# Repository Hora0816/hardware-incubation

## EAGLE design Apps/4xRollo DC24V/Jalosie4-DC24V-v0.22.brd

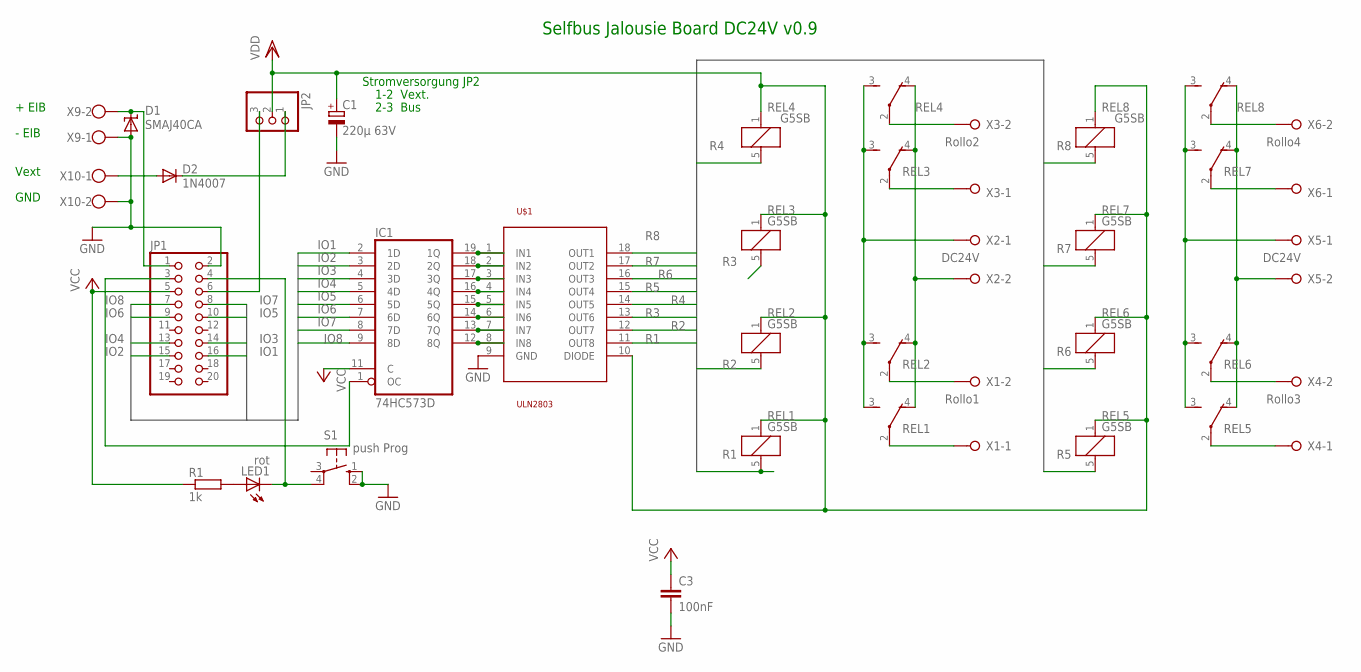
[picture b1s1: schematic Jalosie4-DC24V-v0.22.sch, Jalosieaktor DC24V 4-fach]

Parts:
C1: 220µ 63V; TT5D10
C3: 100nF; C050-024X044
D1: SMAJ40CA; SMBJ
D2: 1N4007; DO41-10
IC1: 74HC573D; SO20W
JP1: PINHD-2X10; 2X10
JP2: PINHD-1X3; 1X03
LED1: rot; LED3MM
R1: 1k; 0204/7
REL1, REL2, REL3, REL4, REL5, REL6, REL7, REL8: G5SB
S1: push Prog; B3F-10XX
U$1: ULN2803; SO18L
X1: Rollo1; W237-132
X2, X5: DC24V; W237-132
X3: Rollo2; W237-132
X4: Rollo3; W237-132
X6: Rollo4; W237-132
X9, X10: W237-102

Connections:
GND: C1.-, C3.2, D1.A, IC1.10 (GND), JP1.2, S1.1 (S), S1.2 (S1), U$1.9 (GND), X9.1, X10.2
IO1: IC1.2 (1D), JP1.16
IO2: IC1.3 (2D), JP1.15
IO3: IC1.4 (3D), JP1.14
IO4: IC1.5 (4D), JP1.13
IO5: IC1.6 (5D), JP1.10
IO6: IC1.7 (6D), JP1.9
IO7: IC1.8 (7D), JP1.8
IO8: IC1.9 (8D), JP1.7
unnamed: REL1.4 (O), REL2.4 (O), REL3.4 (O), REL4.4 (O), X2.2
unnamed: REL4.2, X3.2
unnamed: REL2.2, X1.2
unnamed: REL1.2, X1.1
unnamed: REL3.2, X3.1
unnamed: REL5.4 (O), REL6.4 (O), REL7.4 (O), REL8.4 (O), X5.2
unnamed: REL5.3 (S), REL6.3 (S), REL7.3 (S), REL8.3 (S), X5.1
unnamed: REL7.2, X6.1
unnamed: REL8.2, X6.2
unnamed: JP1.4, LED1.K (C), S1.4 (P1)
unnamed: LED1.A, R1.2
unnamed: REL1.3 (S), REL2.3 (S), REL3.3 (S), REL4.3 (S), X2.1
unnamed: REL6.2, X4.2
unnamed: REL5.2, X4.1
unnamed: D2.A, X10.1
unnamed: JP1.6, JP2.3
unnamed: D1.C, JP1.1, X9.2
unnamed: IC1.19 (1Q), U$1.1 (IN1)
unnamed: IC1.18 (2Q), U$1.2 (IN2)
unnamed: IC1.17 (3Q), U$1.3 (IN3)
unnamed: IC1.16 (4Q), U$1.4 (IN4)
unnamed: IC1.15 (5Q), U$1.5 (IN5)
unnamed: IC1.14 (6Q), U$1.6 (IN6)
unnamed: IC1.13 (7Q), U$1.7 (IN7)
unnamed: IC1.12 (8Q), U$1.8 (IN8)
unnamed: D2.C, JP2.1
unnamed: IC1.1 (OC), JP1.3
R1: REL1.5 (2), U$1.11 (OUT8)
R2: REL2.5 (2), U$1.12 (OUT7)
R3: REL3.5 (2), U$1.13 (OUT6)
R4: REL4.5 (2), U$1.14 (OUT5)
R5: REL5.5 (2), U$1.15 (OUT4)
R6: REL6.5 (2), U$1.16 (OUT3)
R7: REL7.5 (2), U$1.17 (OUT2)
R8: REL8.5 (2), U$1.18 (OUT1)
VCC: C3.1, IC1.11 (C), IC1.20 (VCC), JP1.5, R1.1
VDD: C1.+, JP2.2, REL1.1, REL2.1, REL3.1, REL4.1, REL5.1, REL6.1, REL7.1, REL8.1, U$1.10 (DIODE)

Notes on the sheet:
+ EIB
- EIB
Vext
GND
1-2 Vext.
2-3 Bus
Stromversorgung JP2
Selfbus Jalousie Board DC24V v0.9

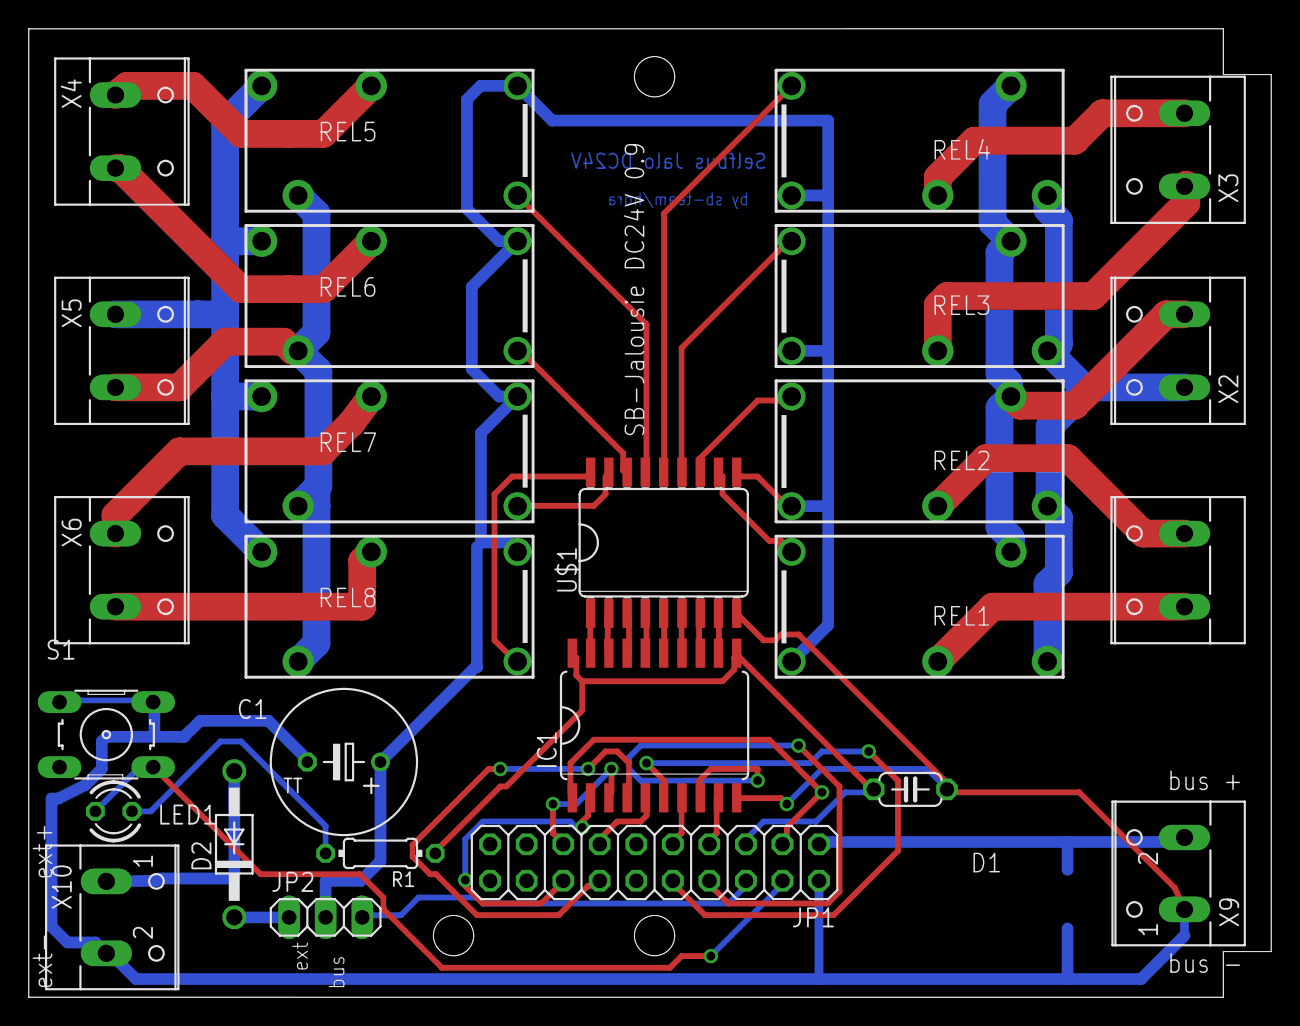
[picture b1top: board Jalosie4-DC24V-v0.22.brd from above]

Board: 2 copper layers, 86.3 x 67.3 mm, 27 parts (1 on the bottom side), 46 nets.

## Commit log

2021-08-16 Create 4xRollo DC24V
2021-08-16 draft 4rollo dc24v
